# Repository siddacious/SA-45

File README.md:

# SA-45 - Useful info for playing doctor with your robot friend

All Software is released under the MIT license. See [MIT.txt](MIT.txt)

All Schematics and artwork is released as CC-BY-SA 4.0. See [CC-BY-SA_40.txt](CC-BY-SA_40.txt)

* [`droid-bb8_schematic.pdf`](droid-bb8_schematic.pdf) by @russdill
* [`nrf_extract/`](nrf_extract/) by @ruthsaurian
* [`nrf_extract_edits`](nrf_extract_edits/) by @siddacious and @ruthsaurian
* all other content by @siddacious

## More cool stuff
* by @russdill [here](https://github.com/russdill/droid_depot)
* by @ruthsaurian [here](https://github.com/ruthsarian/pxt-swge-beacon)
* SWGE discord: https://discord.gg/nsa9wCz

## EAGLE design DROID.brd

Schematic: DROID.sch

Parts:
C11, C16, C18, C21, C23, C24, C25, C26, C27, C29, C31, C33, C34, C35, C36, C38, C39: CAP_CERAMIC0603_NO; 0603-NO
C17, C19, C20A, C22A, C28: CAP_CERAMIC_0805MP; _0805MP
C37: 100uF; PANASONIC_D
D14: DIODESOD-323; SOD-323
F1: PTC1812
JP1, JP2, JP3, JP4, JP5, JP6: HEADER-1X2ROUND; 1X02_ROUND
JP7, JP8, JP9: HEADER-1X3ROUND; 1X03_ROUND
JP10, JP11, JP12: HEADER-1X4ROUND; 1X04_ROUND
JP13, JP14: HEADER-1X5ROUND; 1X05_ROUND
JP15: HEADER-1X6ROUND; 1X06_ROUND
L9, L13, L14: INDUCTOR0805-NO; 0805-NO
L11, L12: INDUCTOR0603_NO; 0603-NO
Q6, Q10, Q13, Q14: TRANSISTOR_PNPSOT23-REFLOW; SOT23-R
Q11, Q12: TRANSISTOR_NPNWIDE; SOT23-WIDE
R5: 330; 0603-NO
R6, R7, R22, R29, R49, R51, R52, R54, R55, R60, R64, R66: 100; 0603-NO
R18, R23, R68: 10K; 0603-NO
R25, R61: 47K; 0603-NO
R26, R30, R76, R77: 0; 0603-NO
R27, R99, R100: 1K; 0603-NO
R43, R44, R45, R47_OR_42, R62, R63, R71: 100K; 0603-NO
R59: 300K; 0603-NO
R81: 470; _0805MP
U7, U8: ME62XX; SOT89
U$1, U$2, U$3: AM1037A; SOIC8_208MIL
U$4: KNRF51822_A24; KNRF51822
U$5: GPCD9TP340A_DROID; GPCD9TP340A

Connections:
3.3V: C24.2, C25.2, C36.2, R25.1, R77.1, R77.2, U8.2 (VOUT), U8.2@1 (VOUT)
9V_IN: C34.2, L13.2, Q10.2 (E), R54.1, U7.1 (VSS)
BAT+: F1.P$2 (2), JP2.2
DET: JP15.3, U$5.29
GND: C11.1, C16.1, C17.1, C18.1, C19.1, C20A.1, C21.1, C22A.1, C23.1, C24.1, C25.1, C26.2, C27.1, C28.1, C29.1, C31.1, C33.1, C34.1, C35.1, C36.1, C37.-, C38.1, C39.1, JP2.1, JP7.2, JP8.2, JP11.2, JP12.1, JP14.2, JP15.6, L14.1, Q11.2 (E), Q12.2 (E), R5.1, R43.1, R44.1, R45.1, R47_OR_42.1, R61.2, R62.1, R63.1, R66.1, R71.1, R81.1, U8.3 (VIN), U$1.6 (GND), U$2.6 (GND), U$3.6 (GND), U$4.P$9 (P0.29), U$5.3, U$5.8, U$5.24, U$5.30, U$5.34
GND_INDUCTED: L14.2, U7.3 (VIN)
HEAD_IN_A: R43.2, U$3.1 (IN_A), U$4.P$3 (P0.23)
HEAD_IN_B: R45.2, U$3.3 (IN_B), U$4.P$4 (P0.24)
HEAD_OUT_A: JP5.2, U$3.7 (OUT_A)
HEAD_OUT_B: JP5.1, U$3.5 (OUT_B)
HED_DET: JP1.1
HE_5V: JP13.5, Q6.3 (C)
H_DET: JP13.1, U$5.13
H_L: JP10.2, R52.1
H_MID: JP10.3, R49.1
H_R: JP10.1, R51.1
LED_B: JP13.2, U$5.12
LED_G: JP13.3, U$5.11
LED_R: JP13.4, U$5.10
LEFT_IN_A: R44.2, U$1.1 (IN_A), U$4.P$5 (P0.25)
LEFT_IN_B: R47_OR_42.2, U$1.3 (IN_B), U$4.P$10 (P0.30)
LEFT_OUT_A: JP3.2, U$1.7 (OUT_A)
LEFT_OUT_B: JP3.1, U$1.5 (OUT_B)
L_ID: JP8.1, R18.1, R22.1
L_LED: JP8.3, R6.1
MM_RESET: C29.2, Q12.3 (C), U$5.5
MM_RESET_OUT: R68.2, R71.2, U$4.P$25 (P0.14)
OFF: JP9.1, R81.2
P0.15: U$4.P$26 (P0.15), U$5.18
P0.17: U$4.P$28 (P0.17), U$5.20
P0.18: U$4.P$29 (P0.18), U$5.21
P0.19: U$4.P$30 (P0.19), U$5.22
PAIR_BTN: JP11.1, U$4.P$24 (P0.13)
PAIR_LED+: JP11.3, U$4.P$22 (P0.11)
PAIR_LED-: JP11.4, R5.2
Q6_B: Q6.1 (B), R27.1
Q10_B: Q10.1 (B), R54.2, R60.2
Q10_C: Q10.3 (C), R59.2
Q11_B: Q11.1 (B), R64.1
Q11_C: Q11.3 (C), R60.1
Q12_B: Q12.1 (B), R68.1
Q13_B: Q13.1 (B), R99.1
Q13_C: Q13.3 (C), R6.2
Q14_B: Q14.1 (B), R100.1
Q14_C: Q14.3 (C), R7.1
R22_B: R22.2, U$4.P$12 (P0.1)
R23_B: R18.2, R23.2, U$4.P$16 (P0.5)
R25_B: R25.2, U$5.6
R27_B: R27.2, U$5.9
R29_B: R29.2, U$4.P$15 (P0.4)
R49_B: R49.2, U$4.P$13 (P0.2)
R51_B: R51.2, U$4.P$2 (P0.22)
R52_B: R52.2, U$4.P$18 (P0.7)
R55_B: R55.2, U$4.P$14 (P0.3)
R61_A: C26.1, R55.1, R59.1, R61.1
R64_B: R64.2, R66.2, U$4.P$23 (P0.12)
R99_B: R99.2, U$5.14
R100_B: R100.2, U$5.15
RIGHT_IN_A: R62.2, U$2.1 (IN_A), U$4.P$19 (P0.8)
RIGHT_IN_B: R63.2, U$2.3 (IN_B), U$4.P$20 (P0.9)
RIGHT_OUT_A: JP4.2, U$2.7 (OUT_A)
RIGHT_OUT_B: JP4.1, U$2.5 (OUT_B)
R_ID: JP7.1, R23.1, R29.1
R_LED: JP7.3, R7.2
SCK: JP14.4, JP15.2, U$5.26
SCL: U$5.17
SDA: JP14.3, U$5.16
SI: JP15.5, U$5.28
SICS: U$5.25
SO: JP15.4, U$5.27
SP+: L12.2, U$5.31
SP+_OUT: C38.2, JP6.1, L12.1
SP-: L11.2, U$5.33
SP-_OUT: C39.2, JP6.2, L11.1
SWCLK: JP12.2, U$4.P$27 (P0.16), U$5.19
SWDIO: D14.A, JP12.3, U$4.P$31 (P0.20)
U8_VIN: C35.2, L9.1, U8.1 (VSS)
VCC_3: JP1.2, JP10.4, U$4.P$11 (P0.00)
VCC_ON: C37.+, D14.C, JP9.2, L13.1
VCV_M: C16.2, C17.2, C18.2, C19.2, C27.2, C28.2, F1.P$1 (1), JP9.3, U$1.4 (VCC), U$2.4 (VCC), U$3.4 (VCC)
VPP: JP14.1, U$5.1

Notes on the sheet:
LEFT
HEAD
should be 2920
Why is C11 all the way over here?!
TODO: * More cleanup * Change H-Bridge Symbol to have out on the other side and pins closer to real life * Check actual voltages * Try to identify voltage dividers * Re-Check SWDIO to Diode * Summarize Connections to NRF and Mystery Module
Totally not an NRF51822
Mystery Module

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
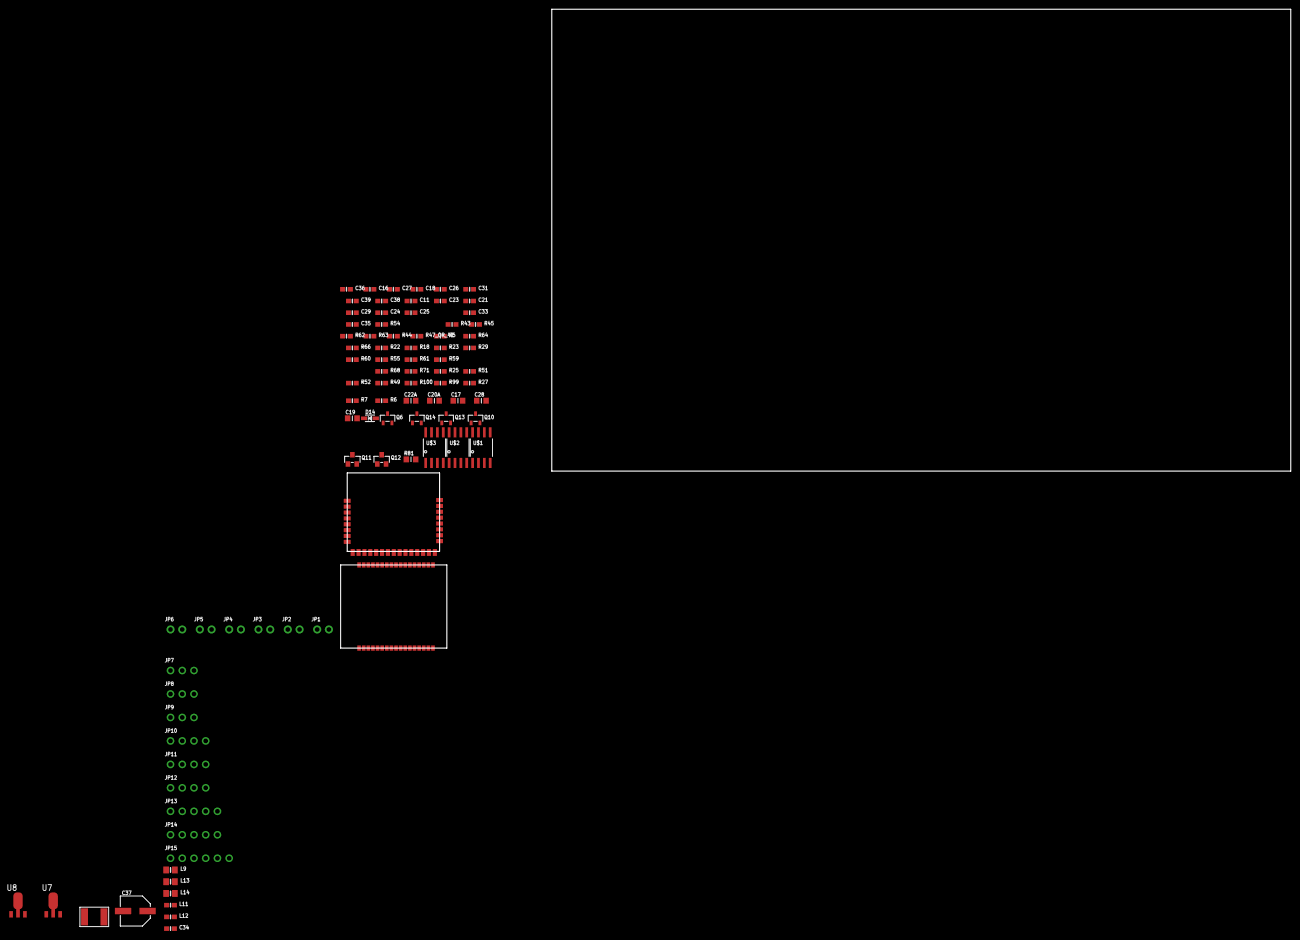
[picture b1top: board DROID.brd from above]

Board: 2 copper layers, 205.7 x 138.3 mm, 88 parts (0 on the bottom side), 80 nets, no tracks yet.

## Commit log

2019-11-03 checking in locally at least
2019-11-03 fixed passive names
2019-11-03 more renames?
2019-11-03 renamed nets to make connections easier
2019-11-03 net name/connection updates
2019-11-03 more nets/conns, addition parts
2019-11-03 all components?
2019-11-04 getti'n close
2019-11-04 done for now
2019-11-04 saving before cleanup
2019-11-04 solved mystery net to motor R, added todos
2019-11-09 adding library export
2019-11-09 moved parts to new lib
2019-11-10 major reorganization
2019-11-11 more organization
2019-11-30 Create CNAME
2019-11-30 Set theme jekyll-theme-minimal
2020-02-09 moar stuff
2020-02-10 more reversing notes
2020-02-10 adding Russ's BB-8 schematic
2020-02-10 adding images. quite large
2020-02-10 adding pdfs for components
2020-02-10 renaming the r-series files for clarity
2020-05-07 adding readme and licenses
2020-05-27 adding in-progress python-ified version of nrf51.h
